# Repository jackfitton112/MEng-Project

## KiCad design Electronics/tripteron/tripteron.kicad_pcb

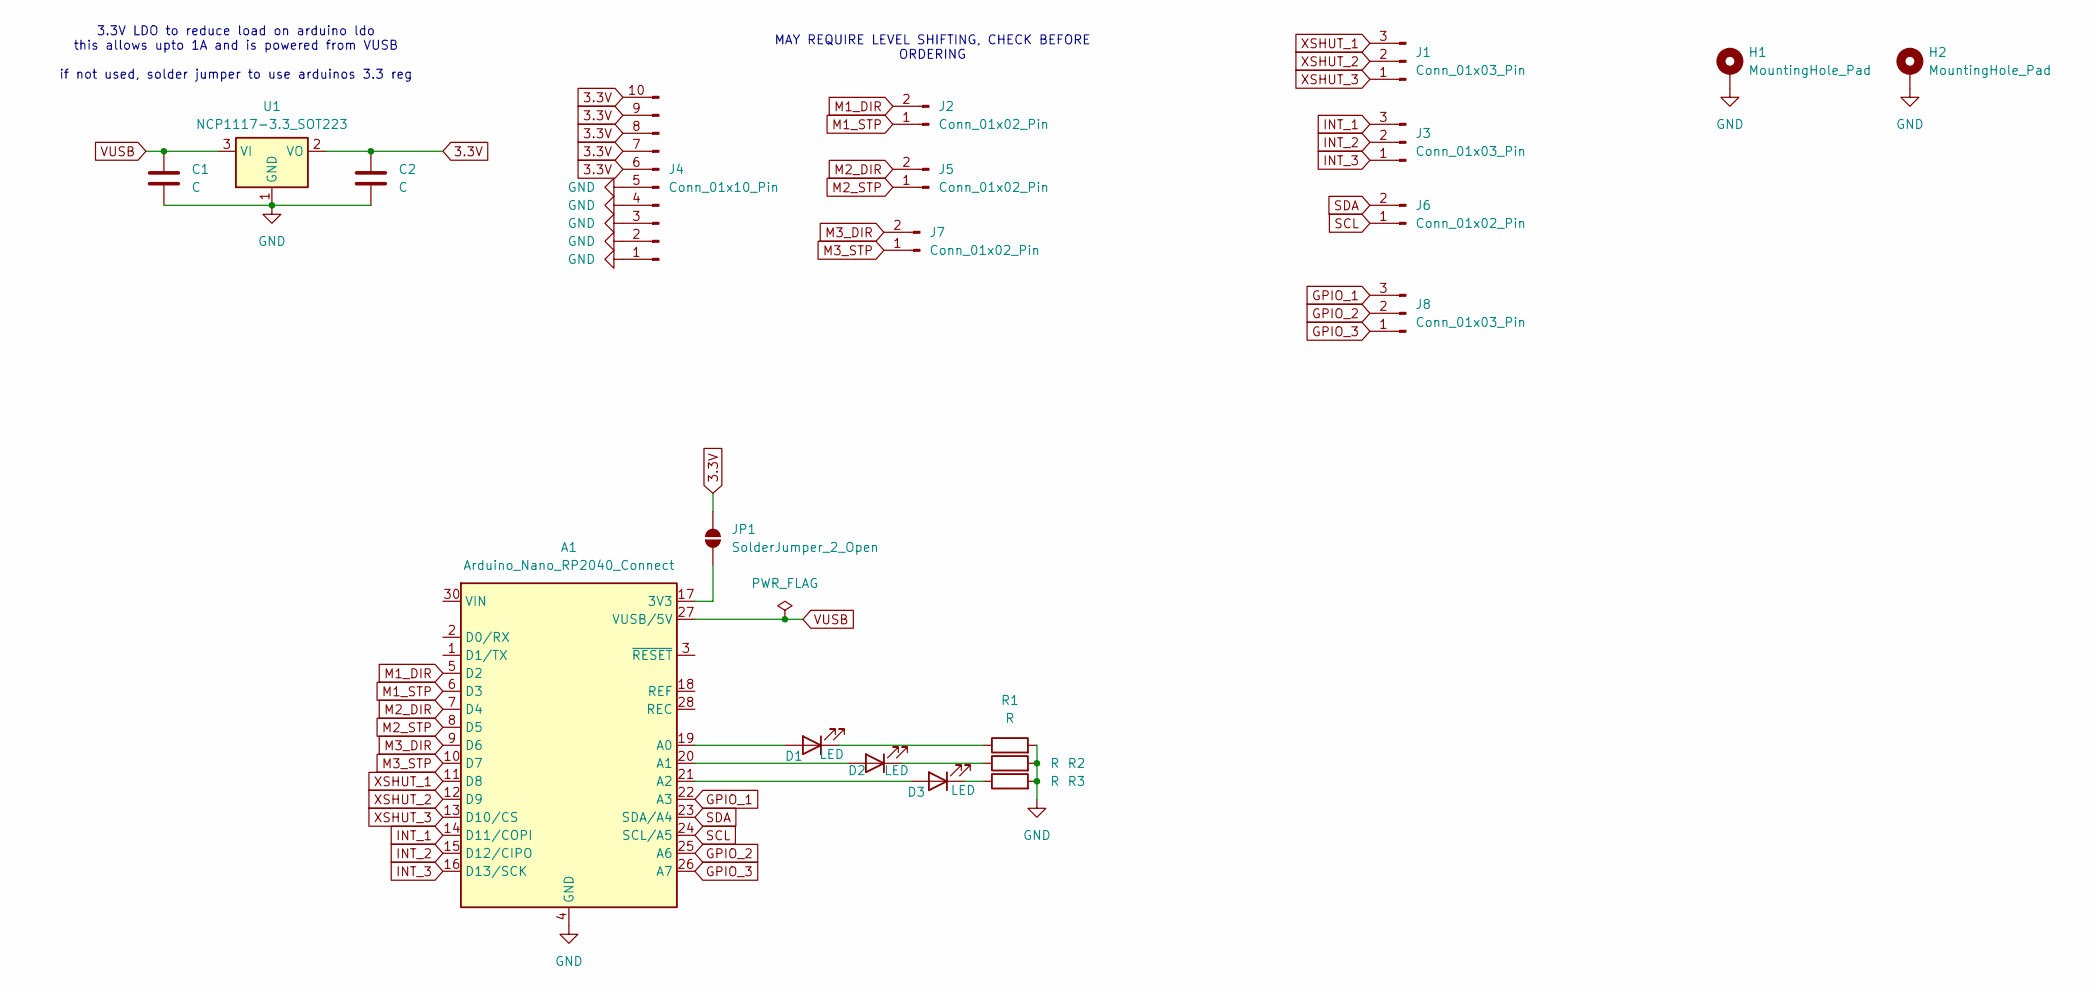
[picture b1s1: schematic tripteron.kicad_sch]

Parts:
A1: Arduino_Nano_RP2040_Connect; Arduino_Nano
C1, C2: C; C_0603_1608Metric_Pad1.08x0.95mm_HandSolder
D1, D2, D3: LED; C_0603_1608Metric_Pad1.08x0.95mm_HandSolder
H1, H2: MountingHole_Pad; MountingHole_3.2mm_M3_DIN965_Pad
J1, J3, J8: Conn_01x03_Pin; PinHeader_1x03_P2.54mm_Vertical
J2, J5, J6, J7: Conn_01x02_Pin; PinHeader_1x02_P2.54mm_Vertical
J4: Conn_01x10_Pin; PinHeader_1x10_P2.54mm_Vertical
JP1: SolderJumper_2_Open; SolderJumper-2_P1.3mm_Open_RoundedPad1.0x1.5mm
R1, R2, R3: R; R_0603_1608Metric_Pad0.98x0.95mm_HandSolder
U1: NCP1117-3.3_SOT223; SOT-223-3_TabPin2

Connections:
3.3V: C2.1, J4.6, J4.7, J4.8, J4.9, J4.10, JP1.2 (B), U1.2 (VO)
GND: A1.4 (GND), A1.29 (GND), C1.2, C2.2, H1.1, H2.1, J4.1, J4.2, J4.3, J4.4, J4.5, R1.2, R2.2, R3.2, U1.1 (GND)
GPIO_1: A1.22 (A3), J8.3
GPIO_2: A1.25 (A6), J8.2
GPIO_3: A1.26 (A7), J8.1
INT_1: A1.14 (D11/COPI), J3.3
INT_2: A1.15 (D12/CIPO), J3.2
INT_3: A1.16 (D13/SCK), J3.1
M1_DIR: A1.5 (D2), J2.2
M1_STP: A1.6 (D3), J2.1
M2_DIR: A1.7 (D4), J5.2
M2_STP: A1.8 (D5), J5.1
M3_DIR: A1.9 (D6), J7.2
M3_STP: A1.10 (D7), J7.1
unnamed: A1.17 (3V3), JP1.1 (A)
unnamed: A1.19 (A0), D1.2 (A)
unnamed: A1.20 (A1), D2.2 (A)
unnamed: A1.21 (A2), D3.2 (A)
unnamed: D1.1 (K), R1.1
unnamed: D2.1 (K), R2.1
unnamed: D3.1 (K), R3.1
SCL: A1.24 (SCL/A5), J6.1
SDA: A1.23 (SDA/A4), J6.2
VUSB: A1.27 (VUSB/5V), C1.1, U1.3 (VI)
XSHUT_1: A1.11 (D8), J1.3
XSHUT_2: A1.12 (D9), J1.2
XSHUT_3: A1.13 (D10/CS), J1.1

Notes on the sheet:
3.3V LDO to reduce load on arduino ldo this allows upto 1A and is powered from VUSB if not used, solder jumper to use arduinos 3.3 reg
MAY REQUIRE LEVEL SHIFTING, CHECK BEFORE ORDERING

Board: 2 copper layers, 21 parts (0 on the bottom side), 27 nets, no tracks yet.

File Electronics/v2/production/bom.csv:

Designator,Footprint,Quantity,Value,LCSC Part #
A1,Arduino_Nano,1,Arduino_Nano_RP2040_Connect,
"C1, C2",0603,2,C,
"D1, D2, D3",0603,3,LED,
"J1, J3, J8",PinHeader_1x03_P2.54mm_Vertical,3,Conn_01x03_Pin,
"J2, J5, J6, J7",PinHeader_1x02_P2.54mm_Vertical,4,Conn_01x02_Pin,
J4,PinHeader_1x10_P2.54mm_Vertical,1,Conn_01x10_Pin,
"R1, R2, R3",0603,3,R,
U1,SOT-223-3_TabPin2,1,NCP1117-3.3_SOT223,

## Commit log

2025-02-23 added CAD files to repo
2025-03-17 week 6 push
2025-03-29 uncertanty and V2 boards
2025-03-30 added joint simulation
2025-03-30 added plot travel
2025-03-30 svg plotter working correctly
2025-03-30 added UART control for driver board
2025-04-01 tsp implemented
2025-04-04 semi-working sim
2025-04-05 added error modeling
2025-04-12 simulation work
2025-04-14 dynamics simulation
2025-04-15 initial controller
